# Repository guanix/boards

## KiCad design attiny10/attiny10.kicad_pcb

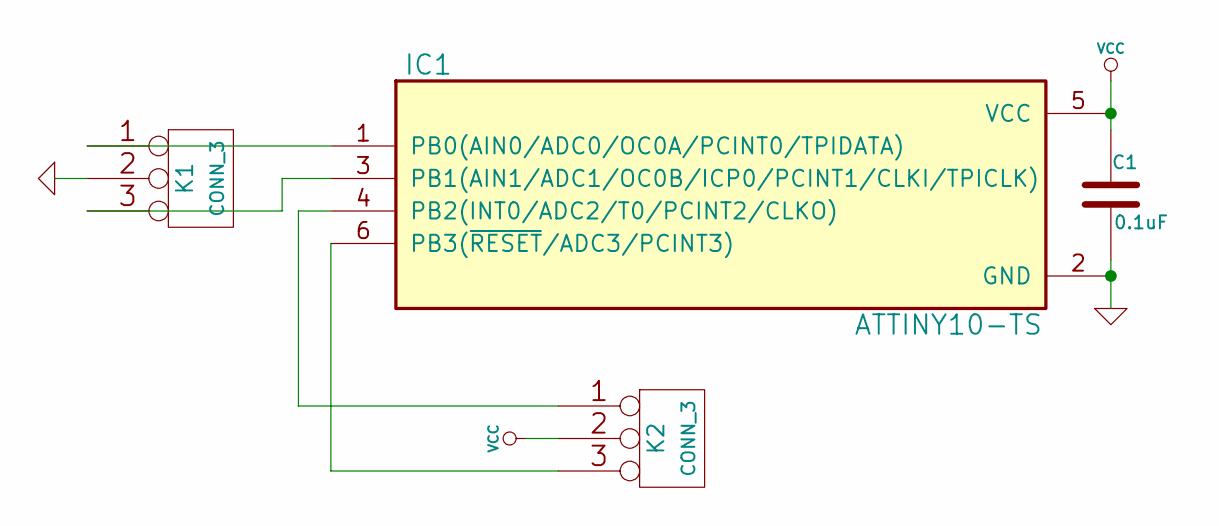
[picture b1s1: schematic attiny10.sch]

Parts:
C1: 0.1uF
IC1: ATTINY10-TS; SOT23-6
K1, K2: CONN_3

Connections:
GND: C1.2, IC1.2 (GND), K1.2 (PM)
unnamed: IC1.1 (PB0(AIN0/ADC0/OC0A/PCINT0/TPIDATA)), K1.1
unnamed: IC1.3 (PB1(AIN1/ADC1/OC0B/ICP0/PCINT1/CLKI/TPI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), K1.3
unnamed: IC1.4 (PB2(INT0/ADC2/T0/PCINT2/CLKO)), K2.1
unnamed: IC1.6 (PB3(~RESET~/ADC3/PCINT3)), K2.3
VCC: C1.1, IC1.5 (VCC), K2.2 (PM)

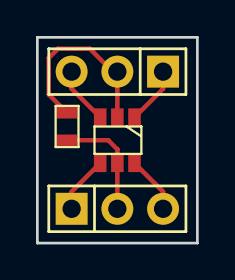
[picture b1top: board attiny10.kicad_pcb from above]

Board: 2 copper layers, 8.9 x 11.4 mm, 4 parts (0 on the bottom side), 6 nets.

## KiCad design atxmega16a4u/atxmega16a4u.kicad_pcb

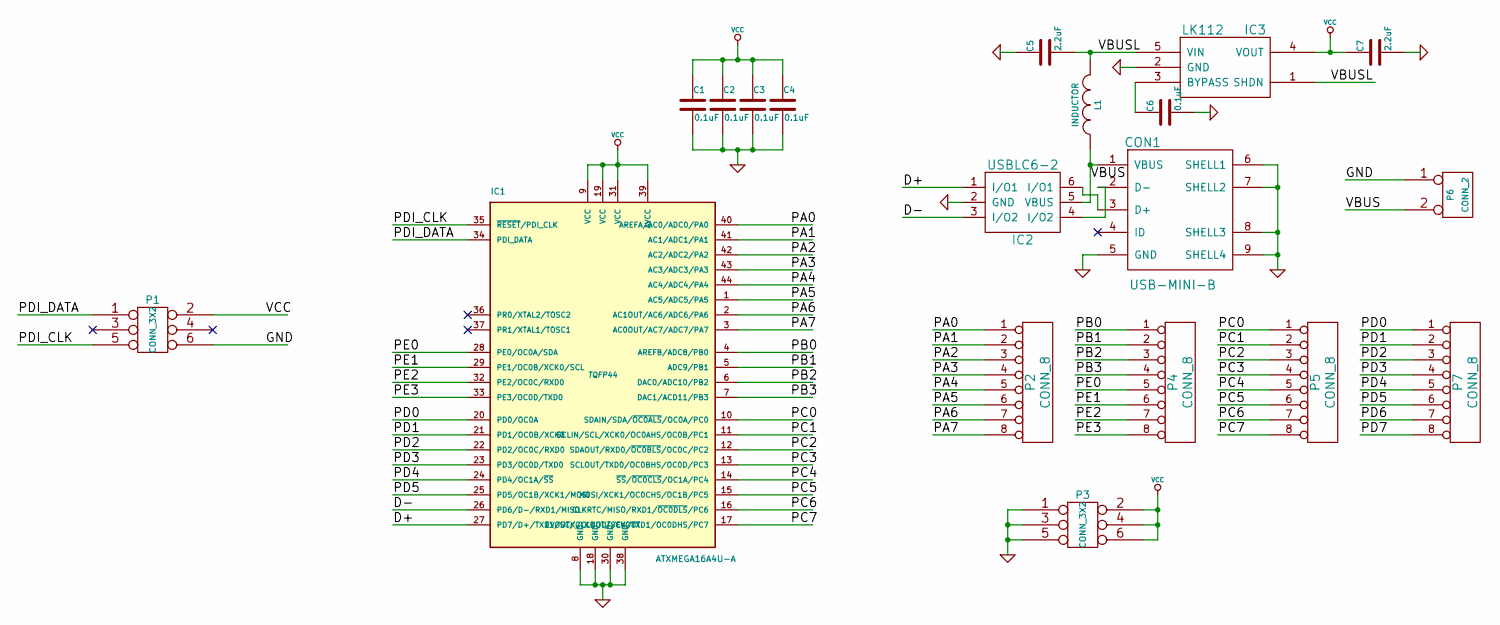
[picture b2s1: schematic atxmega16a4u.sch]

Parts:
C1, C2, C3, C4, C6: 0.1uF
C5, C7: 2.2uF
CON1: USB-MINI-B
IC1: ATXMEGA16A4U-A; TQFP44
IC2: USBLC6-2
IC3: LK112
L1: INDUCTOR
P1, P3: CONN_3X2
P2, P4, P5, P7: CONN_8
P6: CONN_2

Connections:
/D+: IC1.27 (PD7/D+/TXD1/SCK/CLKOUT/EVOUT), IC2.1 (I/O1)
/D-: IC1.26 (PD6/D-/RXD1/MISO), IC2.3 (I/O2)
/PA0: IC1.40 (AREFA/AC0/ADC0/PA0), P2.1
/PA1: IC1.41 (AC1/ADC1/PA1), P2.2
/PA2: IC1.42 (AC2/ADC2/PA2), P2.3
/PA3: IC1.43 (AC3/ADC3/PA3), P2.4
/PA4: IC1.44 (AC4/ADC4/PA4), P2.5
/PA5: IC1.1 (AC5/ADC5/PA5), P2.6
/PA6: IC1.2 (AC1OUT/AC6/ADC6/PA6), P2.7
/PA7: IC1.3 (AC0OUT/AC7/ADC7/PA7), P2.8
/PB0: IC1.4 (AREFB/ADC8/PB0), P4.1
/PB1: IC1.5 (ADC9/PB1), P4.2
/PB2: IC1.6 (DAC0/ADC10/PB2), P4.3
/PB3: IC1.7 (DAC1/ACD11/PB3), P4.4
/PC0: IC1.10 (SDAIN/SDA/~OC0ALS~/OC0A/PC0), P5.1
/PC1: IC1.11 (SCLIN/SCL/XCK0/OC0AHS/OC0B/PC1), P5.2
/PC2: IC1.12 (SDAOUT/RXD0/~OC0BLS~/OC0C/PC2), P5.3
/PC3: IC1.13 (SCLOUT/TXD0/OC0BHS/OC0D/PC3), P5.4
/PC4: IC1.14 (~SS~/~OC0CLS~/OC1A/PC4), P5.5
/PC5: IC1.15 (MOSI/XCK1/OC0CHS/OC1B/PC5), P5.6
/PC6: IC1.16 (CLKRTC/MISO/RXD1/~OC0DLS~/PC6), P5.7
/PC7: IC1.17 (EVOUT/CLKOUT/SCK/TXD1/OC0DHS/PC7), P5.8
/PD0: IC1.20 (PD0/OC0A), P7.1
/PD1: IC1.21 (PD1/OC0B/XCK0), P7.2
/PD2: IC1.22 (PD2/OC0C/RXD0), P7.3
/PD3: IC1.23 (PD3/OC0D/TXD0), P7.4
/PD4: IC1.24 (PD4/OC1A/~SS~), P7.5
/PD5: IC1.25 (PD5/OC1B/XCK1/MOSI), P7.6
/PD6: P7.7
/PD7: P7.8
/PDI_CLK: IC1.35 (~RESET~/PDI_CLK), P1.5
/PDI_DATA: IC1.34 (PDI_DATA), P1.1
/PE0: IC1.28 (PE0/OC0A/SDA), P4.5
/PE1: IC1.29 (PE1/OC0B/XCK0/SCL), P4.6
/PE2: IC1.32 (PE2/OC0C/RXD0), P4.7
/PE3: IC1.33 (PE3/OC0D/TXD0), P4.8
/VBUS: CON1.1 (VBUS), IC2.5 (VBUS), L1.1, P6.2 (PM)
/VBUSL: C5.2, IC3.1 (SHDN), IC3.5 (VIN), L1.2
GND: C1.2, C2.2, C3.2, C4.2, C5.1, C6.2, C7.2, CON1.5 (GND), CON1.6 (SHELL1), CON1.7 (SHELL2), CON1.8 (SHELL3), CON1.9 (SHELL4), IC1.8 (GND), IC1.18 (GND), IC1.30 (GND), IC1.38 (GND), IC2.2 (GND), IC3.2 (GND), P1.6, P3.1, P3.3, P3.5, P6.1
unnamed: C6.1, IC3.3 (BYPASS)
unnamed: CON1.3 (D+), IC2.6 (I/O1)
unnamed: CON1.2 (D-), IC2.4 (I/O2)
VCC: C1.1, C2.1, C3.1, C4.1, C7.1, IC1.9 (VCC), IC1.19 (VCC), IC1.31 (VCC), IC1.39 (AVCC), IC3.4 (VOUT), P1.2, P3.2, P3.4, P3.6

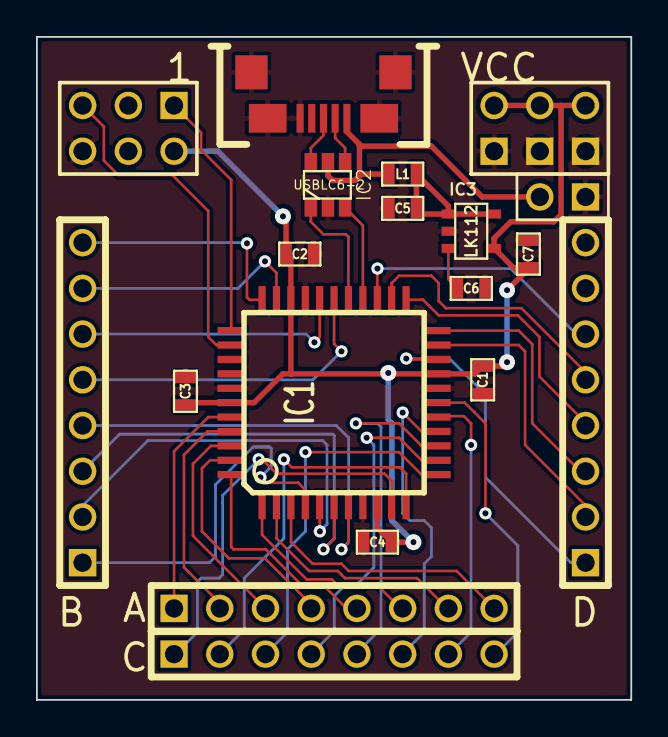
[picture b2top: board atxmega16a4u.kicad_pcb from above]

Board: 2 copper layers, 33.0 x 36.8 mm, 19 parts (0 on the bottom side), 41 nets.

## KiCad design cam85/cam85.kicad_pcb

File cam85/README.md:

# ATtiny85 based shutter timer for keychain spy cameras

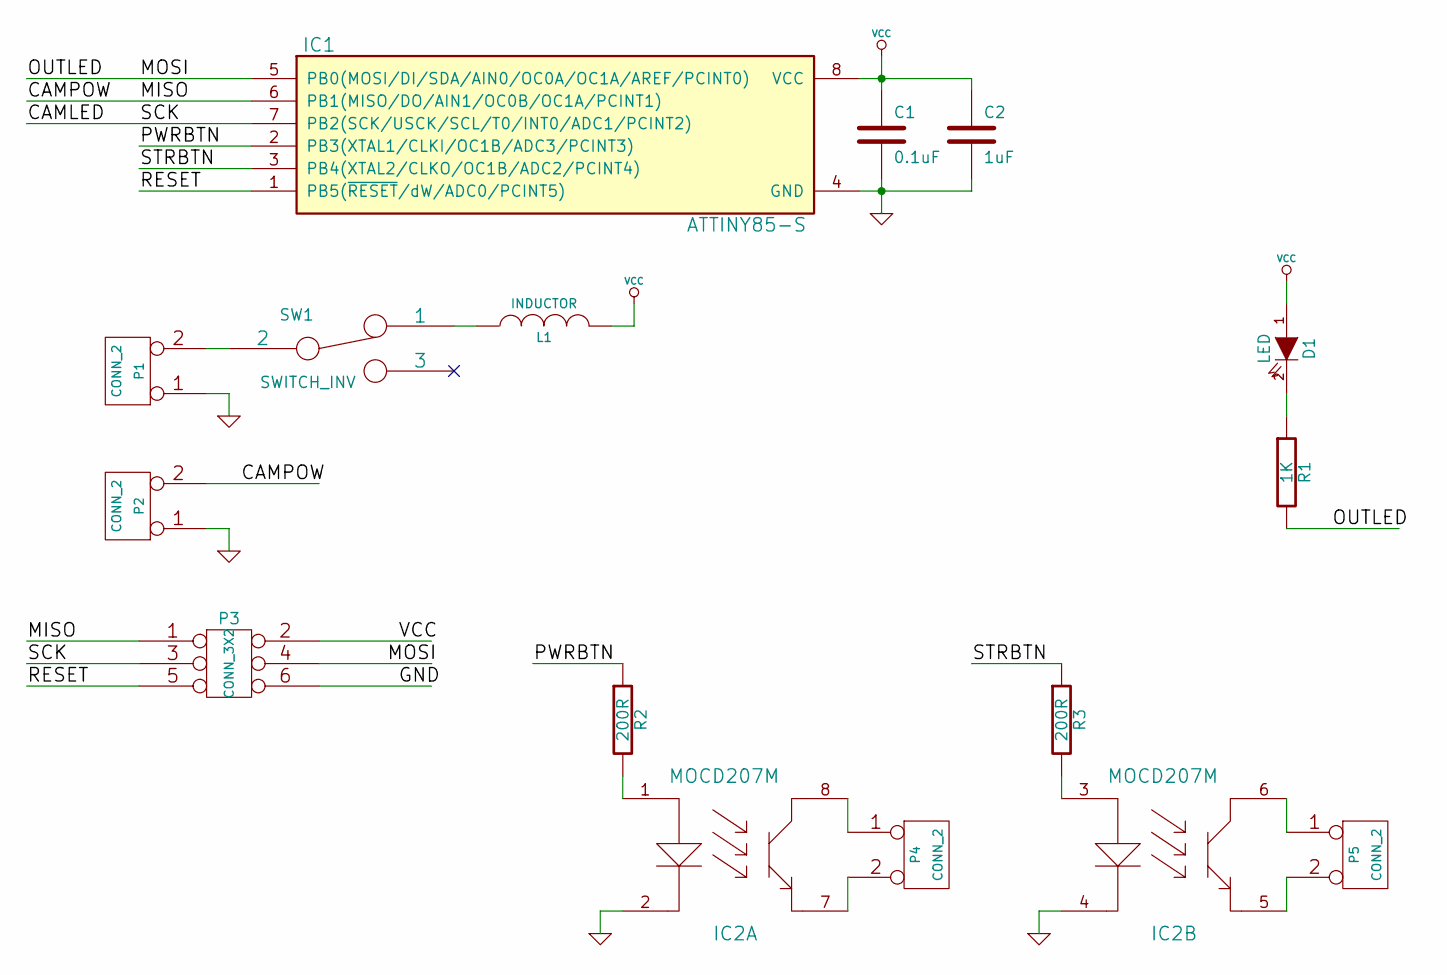
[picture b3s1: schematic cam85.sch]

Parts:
C1: 0.1uF
C2: 1uF
D1: LED
IC1: ATTINY85-S; SO8-200
IC2: MOCD207M
L1: INDUCTOR
P1, P2, P4, P5: CONN_2
P3: CONN_3X2
R1: 1K
R2, R3: 200R
SW1: SWITCH_INV

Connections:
/CAMLED: IC1.7 (PB2(SCK/USCK/SCL/T0/INT0/ADC1/PCINT2)), P3.3
/CAMPOW: IC1.6 (PB1(MISO/DO/AIN1/OC0B/OC1A/PCINT1)), P2.2 (PM), P3.1
/MOSI: IC1.5 (PB0(MOSI/DI/SDA/AIN0/OC0A/OC1A/AREF/PCI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), P3.4, R1.2
/PWRBTN: IC1.2 (PB3(XTAL1/CLKI/OC1B/ADC3/PCINT3)), R2.1
/RESET: IC1.1 (PB5(~RESET~/dW/ADC0/PCINT5)), P3.5
/STRBTN: IC1.3 (PB4(XTAL2/CLKO/OC1B/ADC2/PCINT4)), R3.1
GND: C1.2, C2.2, IC1.4 (GND), IC2.2, IC2.4, P1.1, P2.1, P3.6; also elsewhere on the board
unnamed: IC2.8, P4.1
unnamed: L1.1, SW1.1
unnamed 9: P1.2 (PM), SW1.2; also elsewhere on the board
unnamed: D1.2 (K), R1.1
unnamed: IC2.7, P4.2 (PM)
unnamed: IC2.6, P5.1
unnamed: IC2.3, R3.2
unnamed: IC2.5, P5.2 (PM)
unnamed: IC2.1, R2.2
VCC: C1.1, C2.1, D1.1 (A), IC1.8 (VCC), L1.2, P3.2

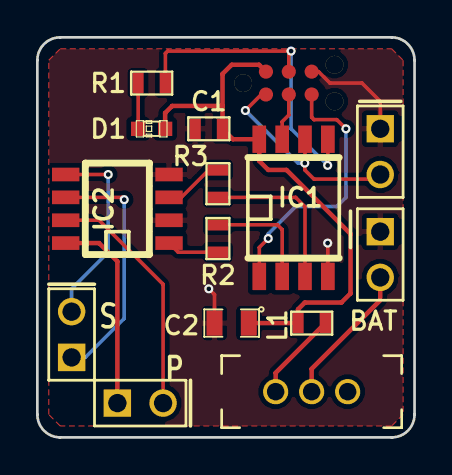
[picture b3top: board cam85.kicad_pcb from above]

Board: 2 copper layers, 21.0 x 22.2 mm, 15 parts (0 on the bottom side), 17 nets.

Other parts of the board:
BAT: CONN_2; PIN_ARRAY_2X1

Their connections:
GND: BAT.1; also elsewhere on the board
unnamed 9: BAT.2; also elsewhere on the board

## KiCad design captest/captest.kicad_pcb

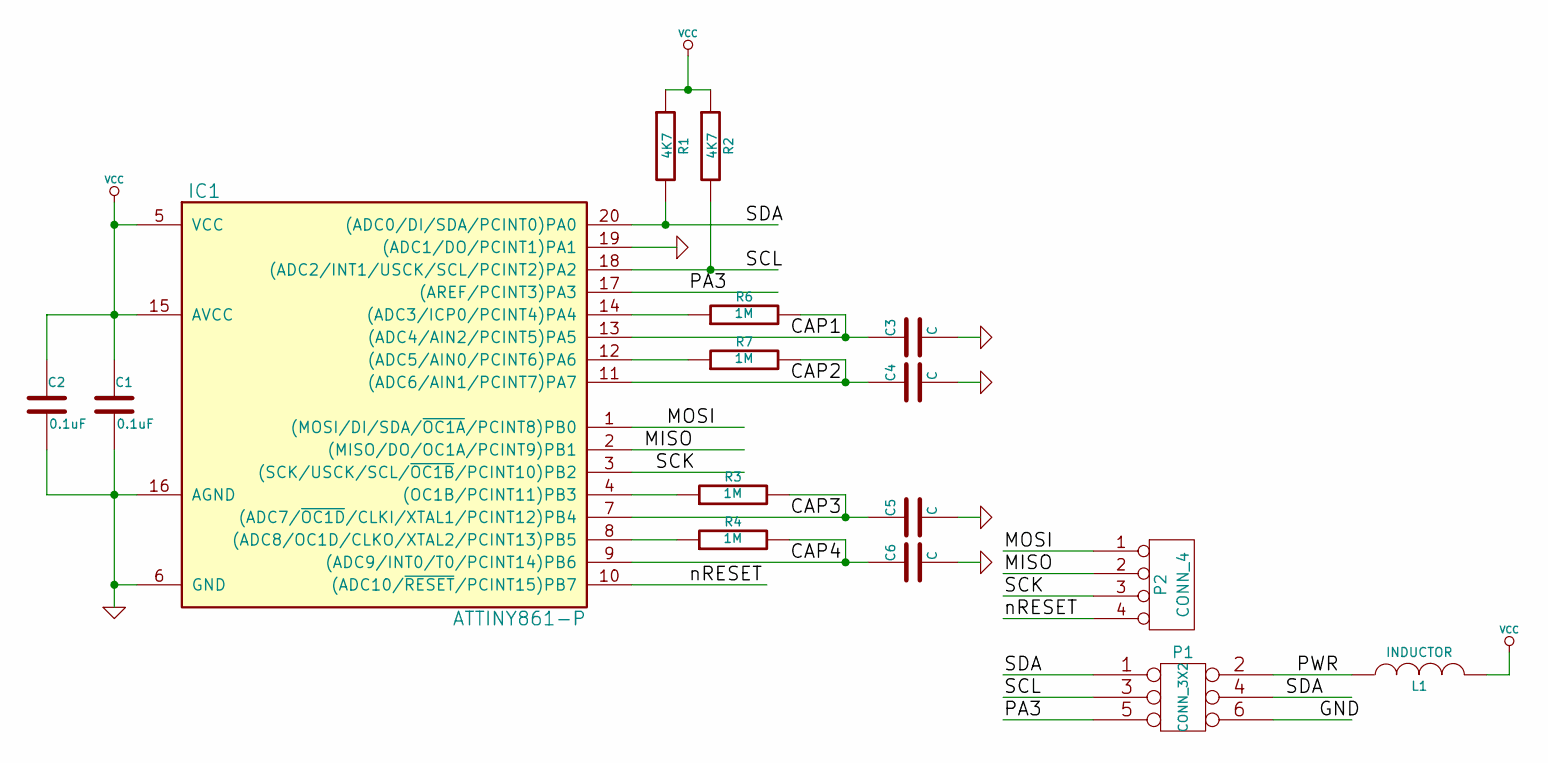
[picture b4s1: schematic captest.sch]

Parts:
C1, C2: 0.1uF
C3, C4, C5, C6: C
IC1: ATTINY861-P; DIP20
L1: INDUCTOR
P1: CONN_3X2
P2: CONN_4
R1, R2: 4K7
R3, R4, R6, R7: 1M

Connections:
/CAP1: C3.1, IC1.13 ((ADC4/AIN2/PCINT5)PA5), R6.2
/CAP2: C4.1, IC1.11 ((ADC6/AIN1/PCINT7)PA7), R7.2
/CAP3: C5.1, IC1.7 ((ADC7/~OC1D~/CLKI/XTAL1/PCINT12)PB4), R3.2
/CAP4: C6.1, IC1.9 ((ADC9/INT0/T0/PCINT14)PB6), R4.2
/MISO: IC1.2 ((MISO/DO/OC1A/PCINT9)PB1), P2.2
/MOSI: IC1.1 ((MOSI/DI/SDA/~OC1A~/PCINT8)PB0), P2.1
/PA3: IC1.17 ((AREF/PCINT3)PA3), P1.5
/PWR: L1.1, P1.2
/SCK: IC1.3 ((SCK/USCK/SCL/~OC1B~/PCINT10)PB2), P2.3
/SCL: IC1.18 ((ADC2/INT1/USCK/SCL/PCINT2)PA2), P1.3, R2.2
/SDA: IC1.20 ((ADC0/DI/SDA/PCINT0)PA0), P1.1, P1.4, R1.2
/nRESET: IC1.10 ((ADC10/~RESET~/PCINT15)PB7), P2.4
GND: C1.2, C2.2, C3.2, C4.2, C5.2, C6.2, IC1.6 (GND), IC1.16 (AGND), IC1.19 ((ADC1/DO/PCINT1)PA1), P1.6
unnamed: IC1.4 ((OC1B/PCINT11)PB3), R3.1
unnamed: IC1.8 ((ADC8/OC1D/CLKO/XTAL2/PCINT13)PB5), R4.1
unnamed: IC1.14 ((ADC3/ICP0/PCINT4)PA4), R6.1
unnamed: IC1.12 ((ADC5/AIN0/PCINT6)PA6), R7.1
VCC: C1.1, C2.1, IC1.5 (VCC), IC1.15 (AVCC), L1.2, R1.1, R2.1

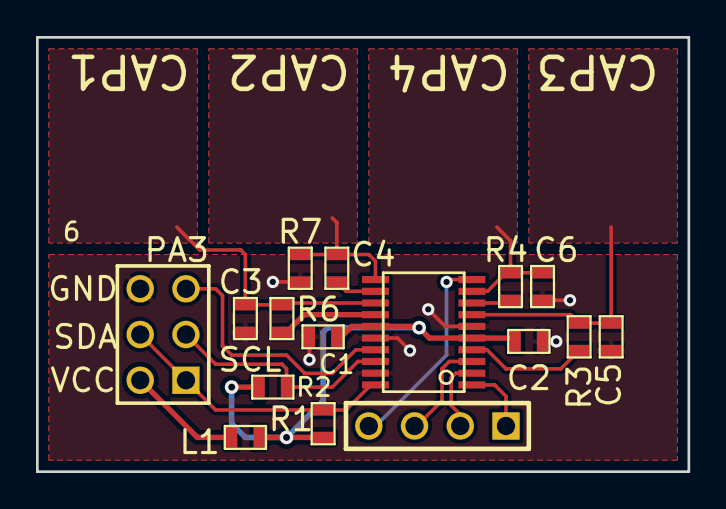
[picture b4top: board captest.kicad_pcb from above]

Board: 2 copper layers, 36.2 x 24.1 mm, 16 parts (0 on the bottom side), 18 nets.

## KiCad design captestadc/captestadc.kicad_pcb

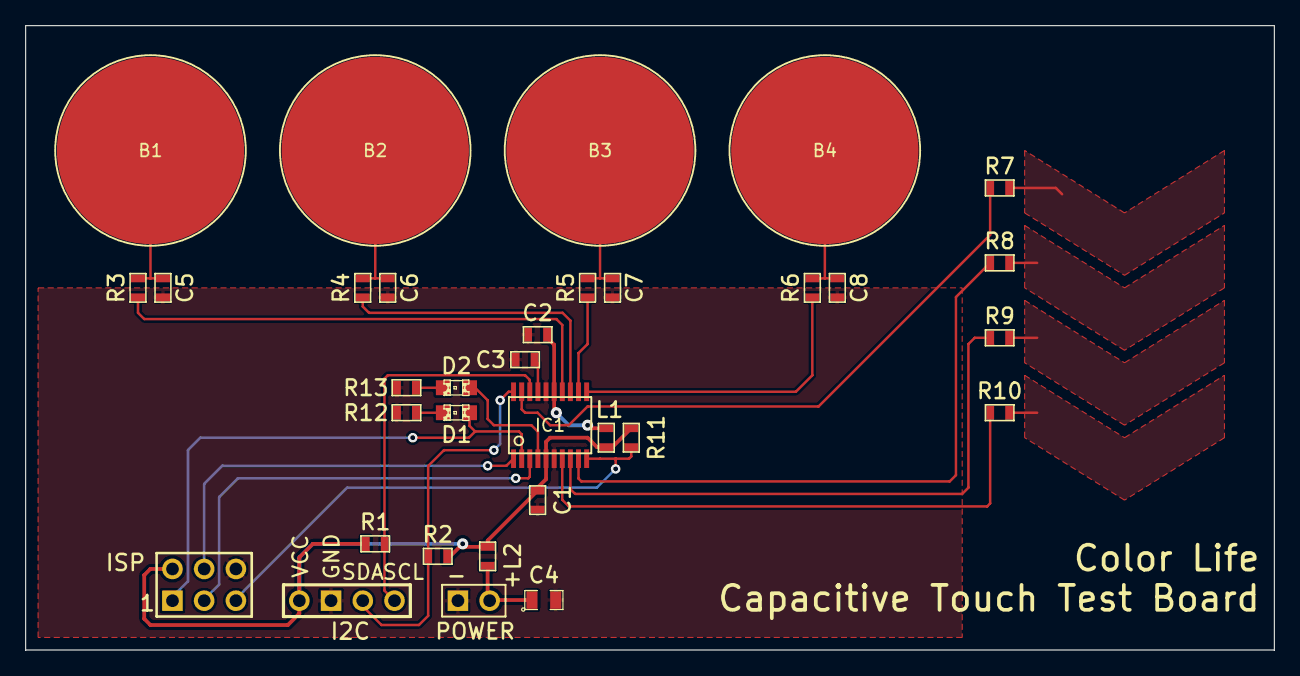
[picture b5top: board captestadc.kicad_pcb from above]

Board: 2 copper layers, 100.0 x 50.0 mm, 33 parts (0 on the bottom side), 26 nets.

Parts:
B1, B2, B3, B4: CONN_1; CAP-BTN
C1, C2, C3: 0.1uF; SM0603
C4: 10uF; SM0805
C5, C6, C7, C8: C; SM0603
D1, D2: LED; LED-0805
I2C: CONN_4; PIN_ARRAY_4x1
IC1: ATTINY861A-X; TSSOP20-4.5MM
ISP: CONN_3X2; pin_array_3x2
L1, L2: INDUCTOR; SM0603
POWER: CONN_2; PIN_ARRAY_2X1
R1, R2: 4K7; SM0603
R3, R4, R5, R6, R7, R8, R9, R10, R11: 10K; SM0603
R12, R13: 1K; SM0603

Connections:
/AREF: C3.1, IC1.17
/AVCC: C2.1, IC1.15, L1.2
/BTN1: IC1.14, R3.1
/BTN2: IC1.13, R4.1
/BTN3: IC1.12, R5.1
/BTN4: IC1.11, R6.1
/LED1: D1.1, IC1.2, ISP.1
/LED2: D2.1, IC1.4
/MOSI: IC1.1, ISP.4
/SCK: IC1.3, ISP.3
/SCL: I2C.4, IC1.18, R1.2
/SDA: I2C.3, IC1.20, R2.2
/SLD1: IC1.19, R7.1
/SLD2: IC1.9, R8.1
/SLD3: IC1.8, R9.1
/SLD4: IC1.7, R10.1
/VIN: C4.1, L2.2, POWER.2
/\RESET: IC1.10, ISP.5, R11.2
GND: C1.1, C2.2, C3.2, C4.2, C5.1, C6.1, C7.1, C8.1, I2C.2, IC1.6, IC1.16, ISP.6, POWER.1, R12.2, R13.2
unnamed: B2.1, C6.2, R4.2
unnamed: B1.1, C5.2, R3.2
unnamed: B3.1, C7.2, R5.2
unnamed: D2.2, R13.1
unnamed: D1.2, R12.1
unnamed: B4.1, C8.2, R6.2
VCC: C1.2, I2C.1, IC1.5, ISP.2, L1.1, L2.1, R1.1, R2.1, R11.1

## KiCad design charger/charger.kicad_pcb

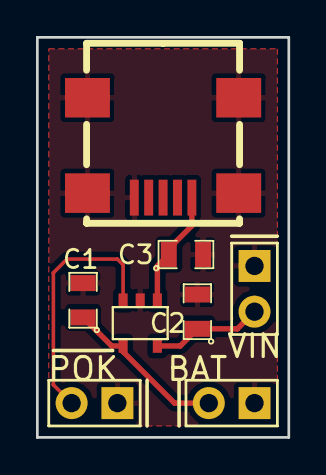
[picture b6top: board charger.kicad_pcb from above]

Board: 2 copper layers, 14.0 x 22.2 mm, 8 parts (0 on the bottom side), 5 nets.

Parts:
C1: C; SM0805
C2, C3: 10uF; SM0805
CON1: USB-MINI-B; MINI-USB-UX60A-MB-5ST
P1: MAX1555; SOT23-5
P2, P3, P4: CONN_2; PIN_ARRAY_2X1

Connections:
/BAT: C1.1, P1.4, P3.1
/VDC: C2.1, P1.5, P2.1
/VUSB: C3.1, CON1.1, P1.1
/\POK: P1.3, P4.1
GND: C1.2, C2.2, C3.2, CON1.5, CON1.6, P1.2, P2.2, P3.2, P4.2

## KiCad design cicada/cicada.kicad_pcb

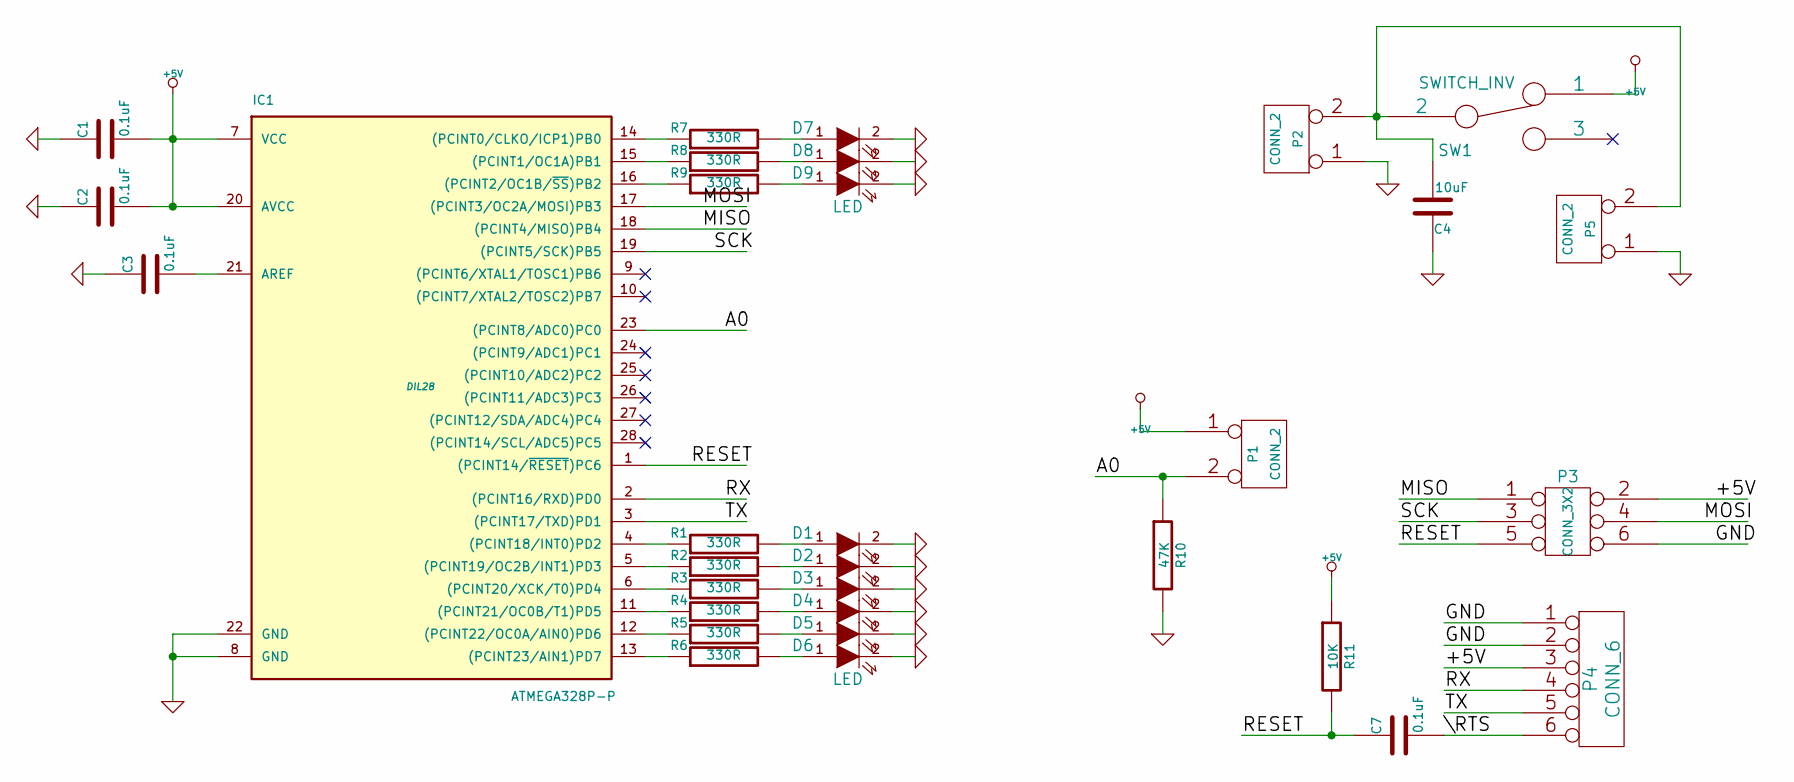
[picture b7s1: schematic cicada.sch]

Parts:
C1, C2, C3, C7: 0.1uF
C4: 10uF
D1, D2, D3, D4, D5, D6, D7, D8, D9: LED
IC1: ATMEGA328P-P; DIL28
P1, P2, P5: CONN_2
P3: CONN_3X2
P4: CONN_6
R1, R2, R3, R4, R5, R6, R7, R8, R9: 330R
R10: 47K
R11: 10K
SW1: SWITCH_INV

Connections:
+5V: C1.2, C2.2, IC1.7 (VCC), IC1.20 (AVCC), P1.1, P3.2, P4.3, R11.1, SW1.1
/A0: IC1.23 ((PCINT8/ADC0)PC0), P1.2 (PM), R10.1
/MISO: IC1.18 ((PCINT4/MISO)PB4), P3.1
/MOSI: IC1.17 ((PCINT3/OC2A/MOSI)PB3), P3.4
/RESET: C7.1, IC1.1 ((PCINT14/~RESET~)PC6), P3.5, R11.2
/RX: IC1.2 ((PCINT16/RXD)PD0), P4.4
/SCK: IC1.19 ((PCINT5/SCK)PB5), P3.3
/TX: IC1.3 ((PCINT17/TXD)PD1), P4.5
/\RTS: C7.2, P4.6
GND: C1.1, C2.1, C3.1, C4.2, D1.2 (K), D2.2 (K), D3.2 (K), D4.2 (K), D5.2 (K), D6.2 (K), D7.2 (K), D8.2 (K), D9.2 (K), IC1.8 (GND), IC1.22 (GND), P2.1, P3.6, P4.1, P4.2, P5.1, R10.2
unnamed: C4.1, P2.2 (PM), P5.2 (PM), SW1.2
unnamed: C3.2, IC1.21 (AREF)
unnamed: IC1.4 ((PCINT18/INT0)PD2), R1.1
unnamed: IC1.5 ((PCINT19/OC2B/INT1)PD3), R2.1
unnamed: IC1.6 ((PCINT20/XCK/T0)PD4), R3.1
unnamed: D1.1 (A), R1.2
unnamed: D2.1 (A), R2.2
unnamed: D3.1 (A), R3.2
unnamed: IC1.11 ((PCINT21/OC0B/T1)PD5), R4.1
unnamed: IC1.12 ((PCINT22/OC0A/AIN0)PD6), R5.1
unnamed: IC1.13 ((PCINT23/AIN1)PD7), R6.1
unnamed: D4.1 (A), R4.2
unnamed: D5.1 (A), R5.2
unnamed: D6.1 (A), R6.2
unnamed: D8.1 (A), R8.2
unnamed: D9.1 (A), R9.2
unnamed: IC1.15 ((PCINT1/OC1A)PB1), R8.1
unnamed: IC1.16 ((PCINT2/OC1B/~SS~)PB2), R9.1
unnamed: D7.1 (A), R7.2
unnamed: IC1.14 ((PCINT0/CLKO/ICP1)PB0), R7.1

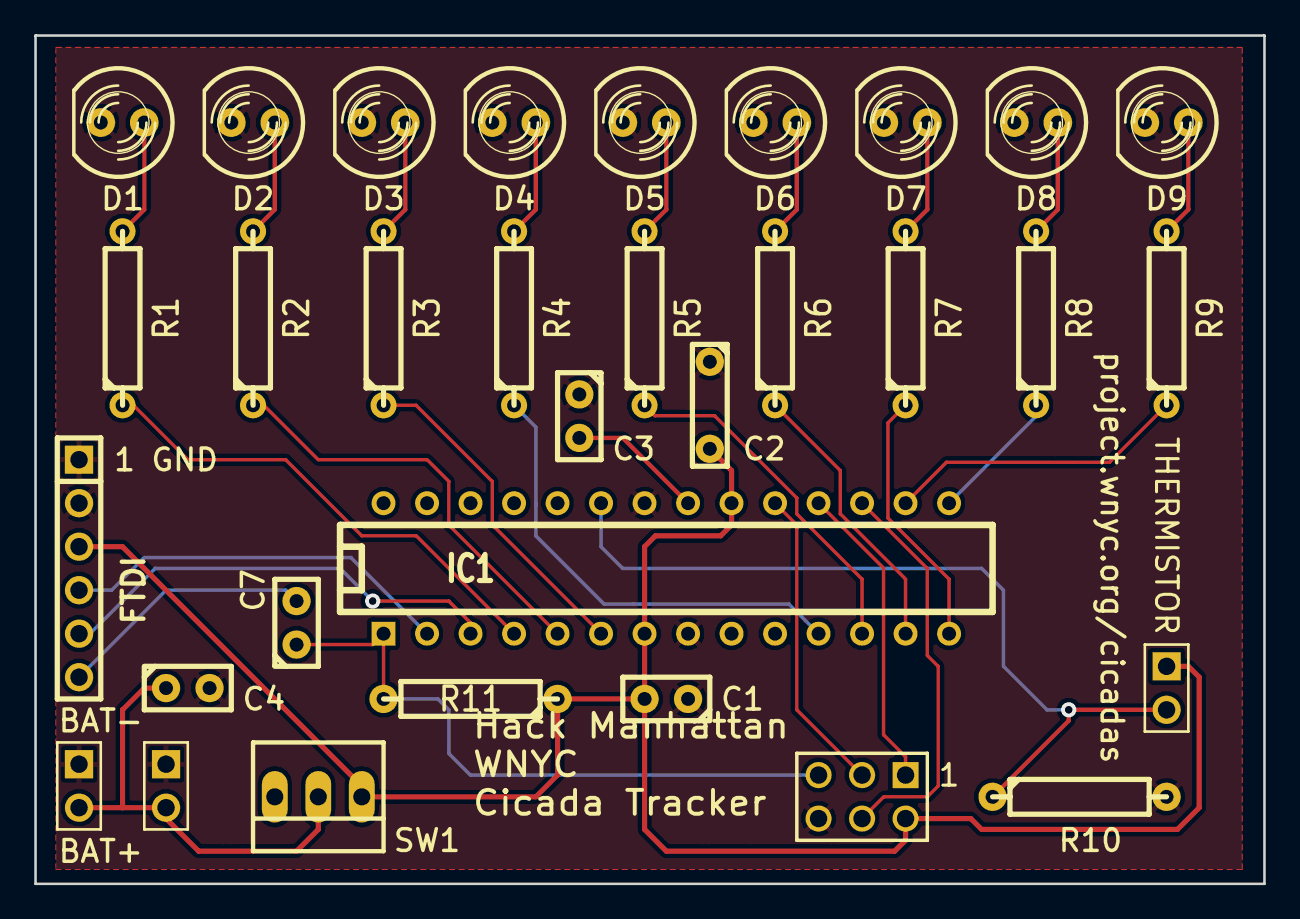
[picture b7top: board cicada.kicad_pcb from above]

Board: 2 copper layers, 71.8 x 49.5 mm, 32 parts (0 on the bottom side), 30 nets.
